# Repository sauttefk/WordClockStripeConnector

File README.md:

# WordClock-Stripe-Connector

Addon für https://www.mikrocontroller.net/articles/WordClock_mit_WS2812

Platine um die Verkabelung der WS2812 LED-Streifen erheblich zu 
vereinfachen und die hierfür notwendige Zeit zu 
verkürzen.

Die Platinen können günstig z.B. bei https://jlcpcb.com/ bestellt werden:  
2-seitig, weißer Stopplack, FR4 0.8mm Materialstärke.

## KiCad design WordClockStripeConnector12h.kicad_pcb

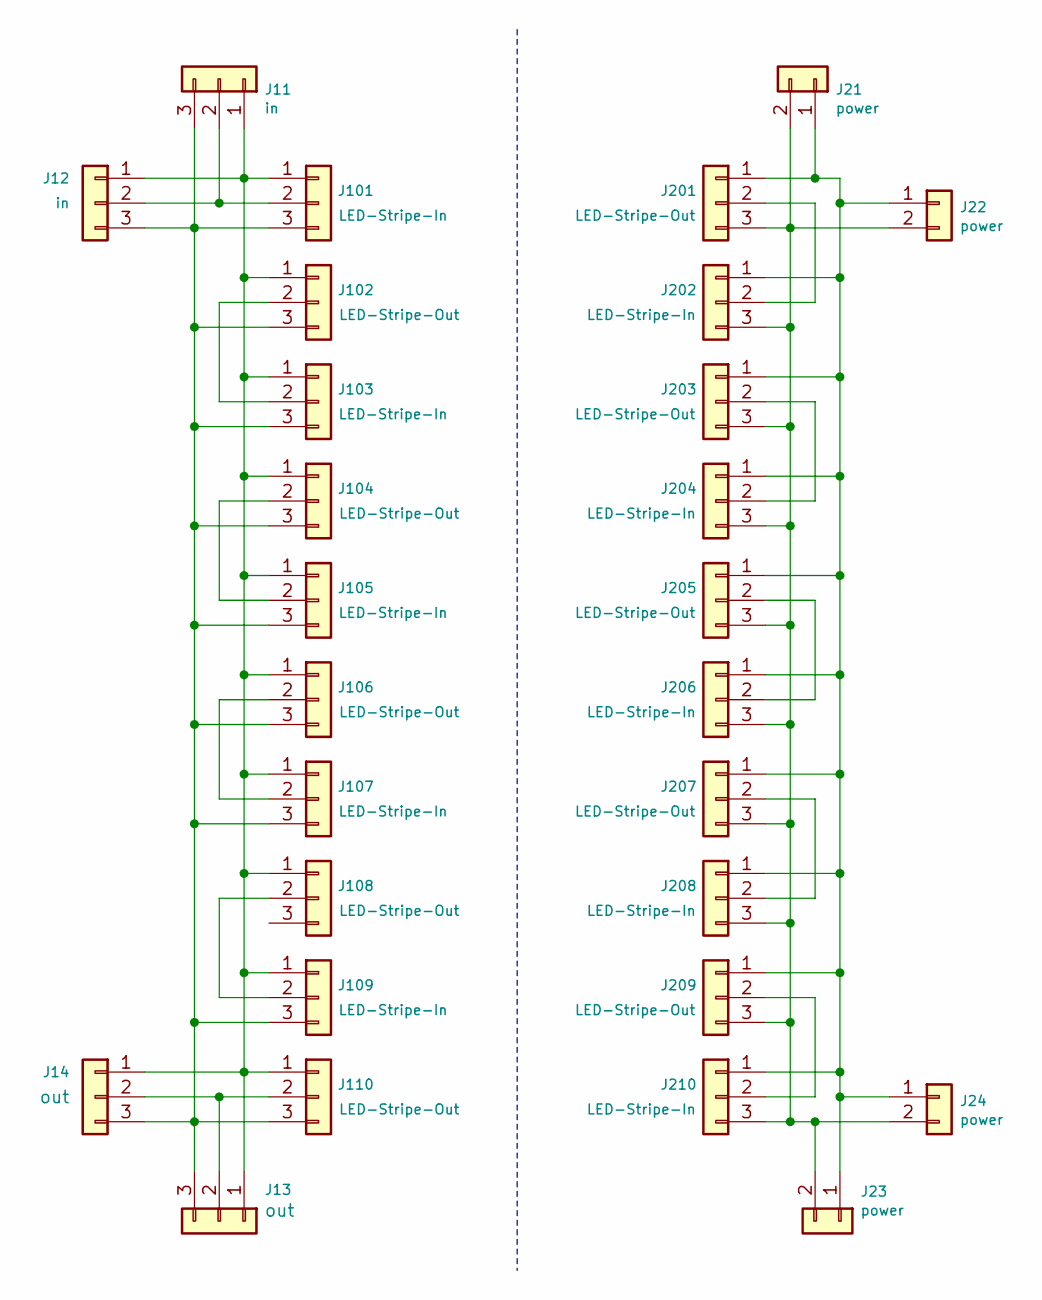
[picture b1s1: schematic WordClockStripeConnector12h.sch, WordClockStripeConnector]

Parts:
J11: in; LED-Stripe-Edge
J12: in; LED-Stripe-Edge-THT
J13: out; LED-Stripe-Edge
J14: out; LED-Stripe-Edge-THT
J21, J23: power; LED-Stripe-Power
J22, J24: power; LED-Stripe-Power-THT
J101, J103, J105, J107, J109, J202, J204, J206, J208, J210: LED-Stripe-In
J102, J104, J106, J108, J110, J201, J203, J205, J207, J209: LED-Stripe-Out

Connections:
unnamed: J11.1, J12.1, J13.1, J14.1, J101.1, J102.1, J103.1, J104.1, J105.1, J106.1, J107.1, J108.1, J109.1, J110.1
unnamed: J11.2, J12.2, J101.2
unnamed: J11.3, J12.3, J13.3, J14.3, J101.3, J102.3, J103.3, J104.3, J105.3, J106.3, J107.3, J109.3, J110.3
unnamed: J102.2, J103.2
unnamed: J104.2, J105.2
unnamed: J106.2, J107.2
unnamed: J108.2, J109.2
unnamed: J13.2, J14.2, J110.2
unnamed: J21.1, J22.1, J23.1, J24.1, J201.1, J202.1, J203.1, J204.1, J205.1, J206.1, J207.1, J208.1, J209.1, J210.1
unnamed: J201.2, J202.2
unnamed: J21.2, J22.2, J23.2, J24.2, J201.3, J202.3, J203.3, J204.3, J205.3, J206.3, J207.3, J208.3, J209.3, J210.3
unnamed: J203.2, J204.2
unnamed: J205.2, J206.2
unnamed: J207.2, J208.2
unnamed: J209.2, J210.2

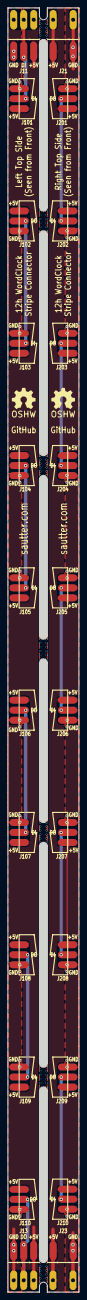
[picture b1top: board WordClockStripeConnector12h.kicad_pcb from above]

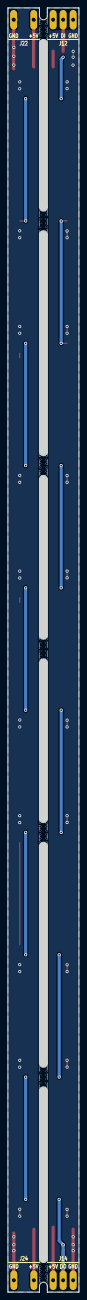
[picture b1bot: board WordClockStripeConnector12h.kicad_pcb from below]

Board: 2 copper layers, 16.0 x 323.5 mm, 28 parts (4 on the bottom side), 15 nets.
